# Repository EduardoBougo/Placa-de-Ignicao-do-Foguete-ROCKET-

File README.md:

# Placa de Ignição do Foguete (ROCKET)
Projeto da placa de acionamento da propulsâo do foguete

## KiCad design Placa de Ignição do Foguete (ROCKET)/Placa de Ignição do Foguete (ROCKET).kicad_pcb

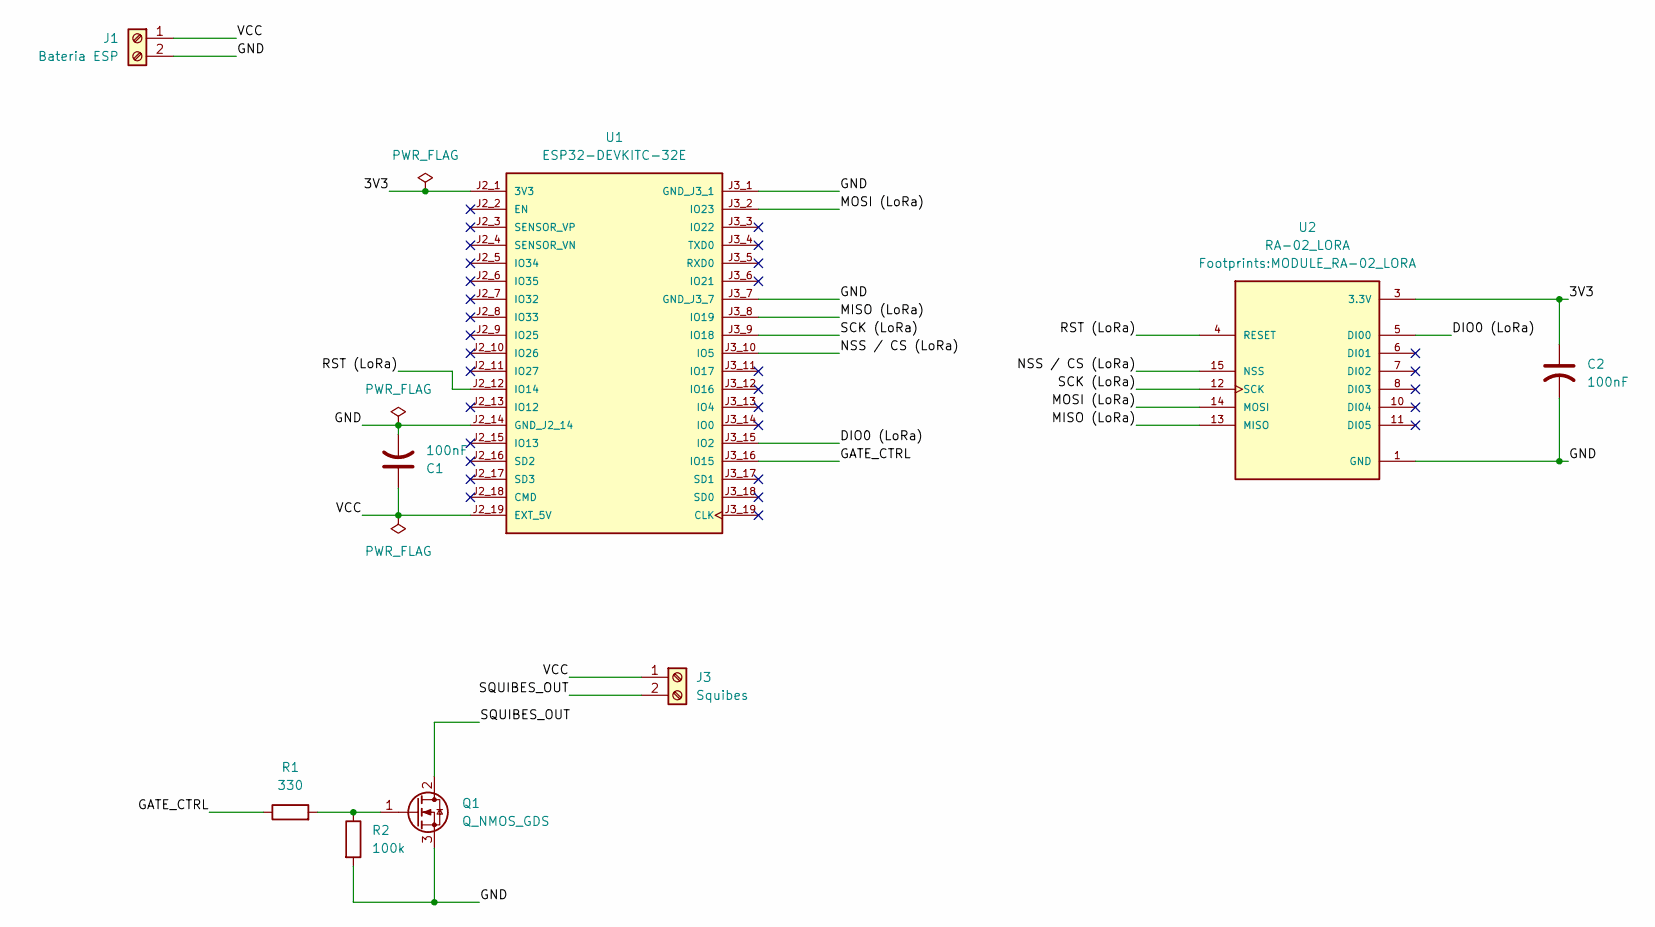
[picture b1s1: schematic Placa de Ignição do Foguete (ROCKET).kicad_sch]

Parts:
C1, C2: 100nF; C_Disc_D5.0mm_W2.5mm_P5.00mm
J1: Bateria ESP; TerminalBlock_Phoenix_MKDS-1,5-2-5.08_1x02_P5.08mm_Horizont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
J3: Squibes; TerminalBlock_Phoenix_MKDS-1,5-2-5.08_1x02_P5.08mm_Horizont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
Q1: Q_NMOS_GDS; TO-220-3_Vertical
R1: 330; R_Axial_DIN0207_L6.3mm_D2.5mm_P7.62mm_Horizontal
R2: 100k; R_Axial_DIN0207_L6.3mm_D2.5mm_P7.62mm_Horizontal
U1: ESP32-DEVKITC-32E; MODULE_ESP32-DEVKITC-32E; PARTREV 1.4
U2: RA-02_LORA; MODULE_RA-02_LORA; PARTREV 2018/03/02

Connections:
/3V3: C2.1, U1.J2_1 (3V3), U2.3 (3.3V)
/DIO0 (LoRa): U1.J3_15 (IO2), U2.5 (DI00)
/GATE_CTRL: R1.1, U1.J3_16 (IO15)
/MISO (LoRa): U1.J3_8 (IO19), U2.13 (MISO)
/MOSI (LoRa): U1.J3_2 (IO23), U2.14 (MOSI)
/NSS / CS (LoRa): U1.J3_10 (IO5), U2.15 (NSS)
/RST (LoRa): U1.J2_12 (IO14), U2.4 (RESET)
/SCK (LoRa): U1.J3_9 (IO18), U2.12 (SCK)
/SQUIBES_OUT: J3.2, Q1.2 (D)
/VCC: C1.1, J1.1, J3.1, U1.J2_19 (EXT_5V)
GND: C1.2, C2.2, J1.2, Q1.3 (S), R2.2, U1.J2_14 (GND_J2_14), U1.J3_1 (GND_J3_1), U1.J3_7 (GND_J3_7), U2.1 (GND), U2.2 (GND), U2.9 (GND), U2.16 (GND)
unnamed: Q1.1 (G), R1.2, R2.1

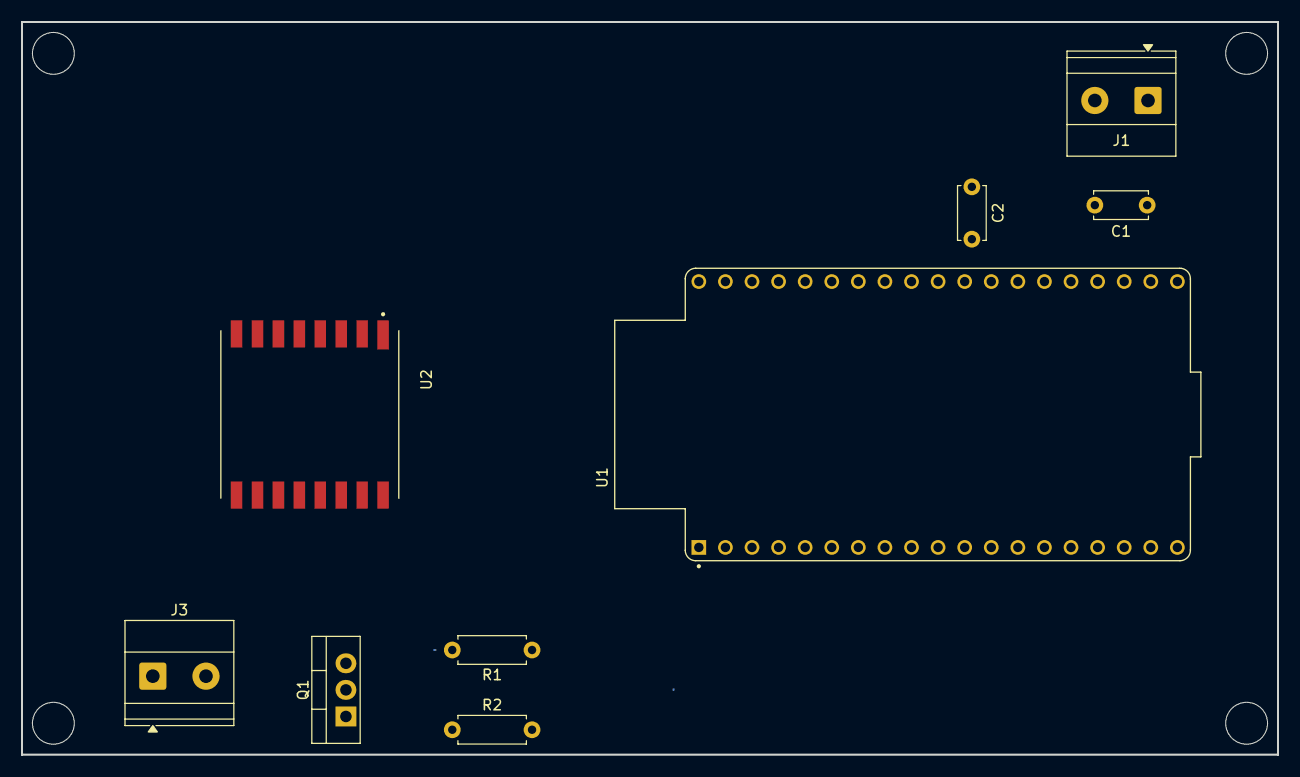
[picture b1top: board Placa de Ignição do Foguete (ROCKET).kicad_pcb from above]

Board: 2 copper layers, 120.0 x 70.0 mm, 9 parts (0 on the bottom side), 12 nets.

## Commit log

2026-06-19 Criação do projeto
2026-06-20 ESP, LoRa e circuito Mosfet
2026-06-23 Teste rapido
    Pode dar cagada
2026-06-25 Correção de problemas com os squibes
2026-06-26 Tentativa inicial de Trilhas lógicas e de alimentação
2026-06-30 to loco
